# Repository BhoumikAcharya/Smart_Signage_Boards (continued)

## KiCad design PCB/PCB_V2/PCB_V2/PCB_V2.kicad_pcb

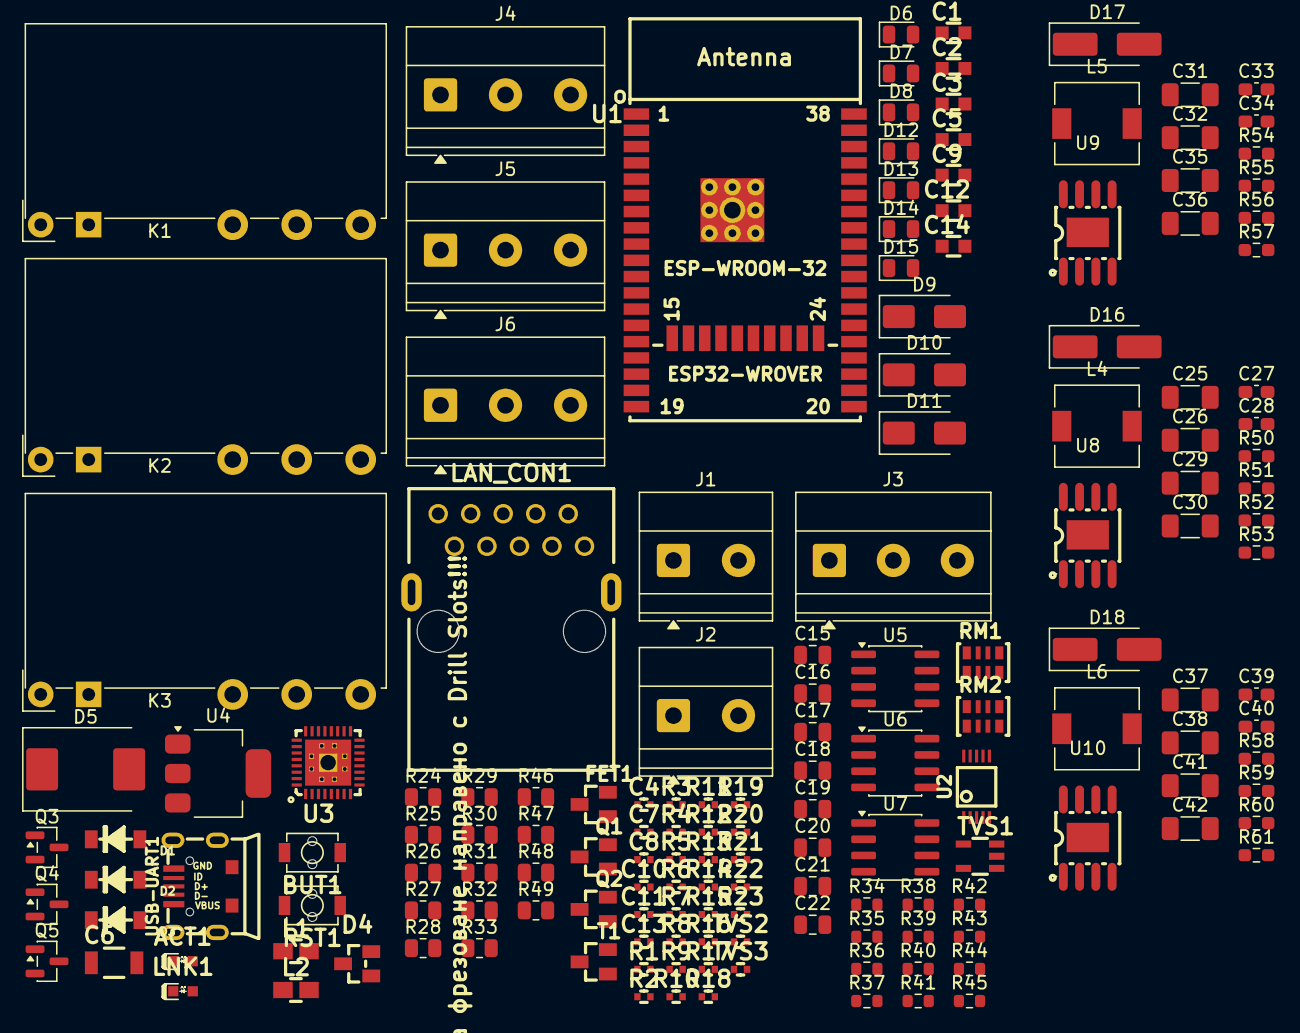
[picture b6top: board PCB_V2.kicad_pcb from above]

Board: 2 copper layers, 161 parts (0 on the bottom side), 116 nets, no tracks yet.

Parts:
ACT1: LED/YELLOW/0603; LED_0603_KA
BUT1: IT1185AU2; IT1185AU2_V2
C1, C3, C5, C9: 22uF/6.3V/20%/X5R/C0603; C_0603_5MIL_DWS
C2: 1uF/10V/20%/X5R/C0603; C_0603_5MIL_DWS
C4, C7, C8, C10, C11, C13: 100nF/10V/20%/X5R/C04020; C_0402_5MIL_DWS
C6: 1nF/2000V/10%/X7R/C1206; C_1206_5MIL_DWS_ISO
C12: 2.2uF/6.3V/10%/X5R/C0603; C_0603_5MIL_DWS
C14: NA(10uF/6.3V/20%/X5R/C0603); C_0603_5MIL_DWS
C15: 10uF; C_0805_2012Metric
C16, C17, C18: 100nF; C_0805_2012Metric
C19, C20, C21: 1nF; C_0805_2012Metric
C22: 22uF; C_0805_2012Metric
C25, C26, C31, C32, C37, C38: 10uF; C_1206_3216Metric_Pad1.33x1.80mm_HandSolder
C27, C33, C39: 100nF; C_0603_1608Metric_Pad1.08x0.95mm_HandSolder
C28, C34, C40: 220pF; C_0603_1608Metric_Pad1.08x0.95mm_HandSolder
C29, C30, C35, C36, C41, C42: 22uF; C_1206_3216Metric_Pad1.33x1.80mm_HandSolder
D1, D2, D3: 1N5819S4(SOD-123); SOD-123_1C-2A_KA
D4: BAT54C(SOT23-3); SOT23-3
D5: SS54; D_SMC
D6, D7, D8, D12, D13, D14, D15: LED; LED_0805_2012Metric
D9, D10, D11: M7; D_SMA
D16, D17, D18: D_SMA_Handsoldering
FET1: WPM2015-3/TR; SOT23
J1: PSU_I/P; TerminalBlock_Phoenix_MKDS-1,5-2-5.08_1x02_P5.08mm_Horizont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
J2: Battery_I/P; TerminalBlock_Phoenix_MKDS-1,5-2-5.08_1x02_P5.08mm_Horizont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
J3: LEDs Ground; TerminalBlock_Phoenix_MKDS-1,5-3_1x03_P5.00mm_Horizontal
J4: Relay_1_Terminal; TerminalBlock_Phoenix_MKDS-1,5-3-5.08_1x03_P5.08mm_Horizont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
J5: Relay_2_Terminal; TerminalBlock_Phoenix_MKDS-1,5-3-5.08_1x03_P5.08mm_Horizont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
J6: Relay_3_Terminal; TerminalBlock_Phoenix_MKDS-1,5-3-5.08_1x03_P5.08mm_Horizont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
K1, K2, K3: FINDER-34.51.7xxx.x019; Relay_SPDT_Finder_34.51_Horizontal
L1, L2: FB0805/600R/2A; L_0805_5MIL_DWS
L4, L5, L6: 6.8uH; L_6.3x6.3_H3
LAN_CON1: RJP-003TC1(LPJ4112CNL)
LNK1: LED/GREEN/0603; LED_0603_KA
Q1, Q2: BC817-40(SOT23); SOT23
Q3, Q4, Q5: BC846; SOT-23
R1, R2, R8, R9, R19, R22: 10k/R0402; R_0402_5MIL_DWS
R3, R13, R14: 1k/R0402; R_0402_5MIL_DWS
R4, R5, R6, R7: 49.9R/1%/R0402; R_0402_5MIL_DWS
R10, R11, R17: 2.2k/R0402; R_0402_5MIL_DWS
R12: 4.7k/R0402; R_0402_5MIL_DWS
R15, R23: NA/R0402; R_0402_5MIL_DWS
R16, R21: 220R/R0402; R_0402_5MIL_DWS
R18: NA(10k/R0402); R_0402_5MIL_DWS
R20: 12.1k/1%/R0402; R_0402_5MIL_DWS
R24, R25, R26, R31, R33: 2.2k; R_0805_2012Metric
R27, R28, R29: 3.3k; R_0805_2012Metric
R30, R32: 10k; R_0805_2012Metric
R34, R35, R36: 300; R_0603_1608Metric
R37, R38, R39: 1k; R_0603_1608Metric
R40, R42: 140k; R_0603_1608Metric
R41, R43, R45: 10k; R_0603_1608Metric
R44: 52.3k; R_0603_1608Metric
R46, R47, R48, R49: 1k; R_0805_2012Metric
R50, R54, R58: 100k; R_0603_1608Metric_Pad0.98x0.95mm_HandSolder
R51, R55, R59: 24.9k; R_0603_1608Metric_Pad0.98x0.95mm_HandSolder
R52, R56, R60: 200k; R_0603_1608Metric_Pad0.98x0.95mm_HandSolder
R53, R57, R61: 68.1k; R_0603_1608Metric_Pad0.98x0.95mm_HandSolder
RM1, RM2: RA1206_(4X0603)_4B8_2.2k; R_MATRIX_4
RST1: IT1185AU2; IT1185AU2_V2
T1: LMUN2211LT1G(SOT-23); SOT23
TVS1: ESDS314DBVR(SOT-23-5); SOT-23-5
TVS2, TVS3: NA(GG0402052R542P); D_0402_5MIL_DWS
U1: ESP32-WROOM-32E-N4; ESP32-WROVER_MODULE
U2: CH340X(MSOP-10); MSOP-10_Pitch-0.5mm_3.00x3.00x1.00mm
U3: LAN8710A-EZC(QFN32); QFN32_EP(33)_5.00x5.00x0.90mm_Pitch_0.50mm
U4: AMS1117-3.3; SOT-223-3_TabPin2
U5, U6, U7: ACS712xLCTR-20A; SOIC-8_3.9x4.9mm_P1.27mm
U8, U9, U10: MP1584EN; SOIC-8_L4.9-W3.9-P1.27-LS6.0-BL-EP3.3
USB-UART1: MISB-SWMM-5B-LF(USB_MICRO); USB-MICRO_MISB-SWMM-5B_LF

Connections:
+3.3V: C1.1, FET1.2, R1.1, R2.1, R15.2, R18.2, R22.1
+3.3VLAN: C5.1, C8.1, FET1.3, L2.1, R19.2, RM1.1.1, RM1.2.1, RM1.3.1, RM1.4.1, RM2.3.1, U3.12 (VDDIO)
+14.5V: D5.2 (A), J1.1, R30.1
/+5V_USB: C3.1, R8.1, U2.7 (VCC), USB-UART1.1 (VBUS)
/D+: U2.1 (UD+), USB-UART1.3 (D+)
/D-: U2.2 (UD-), USB-UART1.2 (D-)
/D_Com: D4.3 (CC), R16.2, R23.2
/ESP_EN: C2.1, D3.2 (A), R2.2, RST1.1, U1.3 (EN)
/GPI34\BUT1: BUT1.1, R22.2, R23.1, U1.6 (GPI34/ADC1_CH6/RTC_GPIO4)
/GPIO0: D4.2 (A2), R15.1, U1.25 (GPIO0/ADC2_CH1/TOUCH1/RTC_GPIO11/CLK_OU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)
/GPIO1\U0TXD: D2.1 (K), U1.35 (GPIO1/U0TXD/CLK_OUT3/EMAC_RXD2)
/GPIO2\HS2_DATA0: D4.1 (A1), U1.24 (GPIO2/ADC2_CH2/TOUCH2/RTC_GPIO12/HSPIWP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)
/GPIO3\U0RXD: D1.2 (A), R9.2, R18.1, U1.34 (GPIO3/U0RXD/CLK_OUT2)
/GPIO17\EMAC_CLK_OUT_180: U1.28 (NC(GPIO17/HS1_DATA5/U2TXD/EMAC_CLK_OUT_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), U3.5 (XTAL1/CLKIN)
/GPIO18\MDIO(RMII): RM1.4.2, U1.30 (GPIO18/VSPICLK/HS1_DATA7), U3.16 (MDIO)
/GPIO19\EMAC_TXD0(RMII): U1.31 (GPIO19/VSPIQ/U0CTS/EMAC_TXD0), U3.22 (TXD0)
/GPIO21\EMAC_TX_EN(RMII): U1.33 (GPIO21/VSPIHD/EMAC_TX_EN), U3.21 (TXEN)
/GPIO22\EMAC_TXD1(RMII): U1.36 (GPIO22/VSPIWP/U0RTS/EMAC_TXD1), U3.23 (TXD1)
/GPIO23\MDC(RMII): U1.37 (GPIO23/VSPID/HS1_STROBE), U3.17 (MDC)
/GPIO25\EMAC_RXD0(RMII): RM1.2.2, U1.10 (GPIO25/DAC_1/ADC2_CH8/RTC_GPIO6/EMAC_RX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), U3.11 (RXD0/MODE0)
/GPIO26\EMAC_RXD1(RMII): RM1.1.2, U1.11 (GPIO26/DAC_2/ADC2_CH9/RTC_GPIO7/EMAC_RX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), U3.10 (RXD1/MODE1)
/GPIO27\EMAC_RX_CRS_DV: RM2.3.2, U1.12 (GPIO27/ADC2_CH7/TOUCH7/RTC_GPIO17/EMAC_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), U3.15 (COL/CRS_DV/MODE2)
/MP1584ENCircuit1/Feedback: R40.2, R41.1, U9.4 (FB)
/MP1584ENCircuit2/Feedback: R42.2, R43.1, U10.4 (FB)
/MP1584ENCircuit/Feedback: R44.2, R45.1, U8.4 (FB)
/RD+: LAN_CON1.3 (RD+), R5.2, TVS1.1 (I/O1), TVS3.1 (IO1), U3.31 (RXP)
/RD-: LAN_CON1.6 (RD-), R4.2, TVS1.5 (I/O4), TVS3.2 (IO2), U3.30 (RXN)
/TD+: LAN_CON1.1 (TD+), R7.2, TVS1.3 (I/O2), TVS2.2 (IO2), U3.29 (TXP)
/TD-: LAN_CON1.2 (TD-), R6.2, TVS1.4 (I/O3), TVS2.1 (IO1), U3.28 (TXN)
AMS1117_O/P: C22.1, R46.2, U1.2 (VDD33(3V3)), U4.2 (VO)
BATT_VD: R32.2, R33.1, U1.5 (GPI39/SENSOR_VN/ADC1_CH3/RTC_GPIO3)
BC1_5_O/P: C15.1, C16.1, C17.1, C18.1, C29.1, C30.1, D9.1 (K), D10.1 (K), D11.1 (K), K1.A1, K2.A1, K3.A1, L4.2, R34.1, R35.1, R36.1, R44.1, R47.2, U4.3 (VI), U5.8 (VCC), U6.8 (VCC), U7.8 (VCC)
BC2_12_O/P_1: C35.1, C36.1, L5.2, R40.1, R48.2, U5.1 (IP+), U5.2 (IP+)
BC3_12_O/P_2: C41.1, C42.1, L6.2, R42.1, R49.2, U6.1 (IP+), U6.2 (IP+), U7.1 (IP+), U7.2 (IP+)
COM1: J4.2, K1.11, U5.3 (IP-), U5.4 (IP-)
COM2: J5.2, K2.11, U6.3 (IP-), U6.4 (IP-)
COM3: J6.2, K3.11, U7.3 (IP-), U7.4 (IP-)
CURRENT_SENSE_1: R24.2, R27.1, U1.9 (GPIO33/XTAL_32K_N/ADC1_CH5/TOUCH8/RTC_G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)
CURRENT_SENSE_2: R25.2, R28.1, U1.7 (GPI35/ADC1_CH7/RTC_GPIO5)
CURRENT_SENSE_3: R26.2, R29.1, U1.8 (GPIO32/XTAL_32K_P/ADC1_CH4/TOUCH9/RTC_G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)
GND: C2.2, C3.2, C4.2, C5.2, C6.1, C7.2, C8.2, C9.2, C10.2, C11.2, C12.2, C13.2, C14.1, C15.2, C16.2, C17.2, C18.2, C19.2, C20.2, C21.2, C22.2, C25.2, C26.2, C29.2, C30.2, C31.2, C32.2, C35.2, C36.2, C37.2, C38.2, C41.2, C42.2, D12.1 (K), D13.1 (K), D14.1 (K), D15.1 (K), D16.2 (A), D17.2 (A), D18.2 (A), J1.2, J2.2, J3.1, J3.2, J3.3, L1.2, LAN_CON1.7 (GND/NC), LAN_CON1.8 (NC/GND), Q3.3 (E), Q4.3 (E), Q5.3 (E), R11.2, R17.1, R20.2, R21.2, R27.2, R28.2, R29.2, R31.2, R33.2, R41.2, R43.2, R45.2, R51.2, R52.2, R53.2, R55.2, R56.2, R57.2, R59.2, R60.2, R61.2, RM2.1.1, RM2.2.1, RST1.2, T1.2 (E), TVS1.2 (GND), U1.1 (GND), U1.15 (GND), U1.38 (GND), U1.39 (THERMAL_PAD), U2.3 (GND), U3.24 (TXD2), U3.25 (TXD3), U3.33 (GND), U4.1 (GND), U5.5 (GND), U6.5 (GND), U7.5 (GND), U8.5 (GND), U8.9 (GND), U9.5 (GND), U9.9 (GND), U10.5 (GND), U10.9 (GND), USB-UART1.5 (GND)
MAIN_OP: C25.1, C26.1, C31.1, C32.1, C37.1, C38.1, D5.1 (K), J2.1, R32.1, R50.1, R54.1, R58.1, U8.7 (VIN), U9.7 (VIN), U10.7 (VIN)
NC1: J4.1, K1.12
NC2: J5.1, K2.12
NC3: J6.1, K3.12
NO1: J4.3, K1.14
NO2: J5.3, K2.14
NO3: J6.3, K3.14
unnamed: ACT1.2 (A), U3.3 (LED1/REGOFF)
unnamed: ACT1.1 (K), R11.1
unnamed: BUT1.2, R21.1
unnamed: C1.2, FET1.1, R1.2, R3.1
unnamed: C28.2, R53.1
unnamed: C34.2, R57.1
unnamed: C40.2, R61.1
unnamed: D1.1 (K), U2.8 (TXD)
unnamed: D2.2 (A), R8.2, U2.9 (RXD)
unnamed: D3.1 (K), Q1.3 (C)
unnamed: D6.2 (A), R34.2
unnamed: D6.1 (K), D9.2 (A), K1.A2, Q3.1 (C)
unnamed: D7.2 (A), R35.2
unnamed: D8.2 (A), R36.2
unnamed: D7.1 (K), D10.2 (A), K2.A2, Q4.1 (C)
unnamed: D8.1 (K), D11.2 (A), K3.A2, Q5.1 (C)
unnamed: D12.2 (A), R46.1
unnamed: D13.2 (A), R47.1
unnamed: D14.2 (A), R48.1
unnamed: D15.2 (A), R49.1
unnamed: C27.1, D16.1 (K), L4.1, U8.1 (SW)
unnamed: C33.1, D17.1 (K), L5.1, U9.1 (SW)
unnamed: C39.1, D18.1 (K), L6.1, U10.1 (SW)
unnamed: L1.1, USB-UART1.0
unnamed: C7.1, C9.1, C10.1, C11.1, L2.2, LAN_CON1.4 (TCT), LAN_CON1.5 (RCT), R4.1, R5.1, R6.1, R7.1, R10.1, U3.1 (VDD2A), U3.27 (VDD1A)
unnamed: C6.2, LAN_CON1.0 (Shield)
unnamed: LNK1.2 (A), R10.2
unnamed: LNK1.1 (K), U3.2 (LED2/NINTSEL)
unnamed: Q1.1 (B), R13.2
unnamed: Q1.2 (E), R14.1, U2.4 (RTS#)
unnamed: Q2.1 (B), R14.2
unnamed: Q2.3 (C), R16.1
unnamed: Q2.2 (E), R12.1, R13.1, U2.6 (TNOW/DTR#)
unnamed: Q3.2 (B), R37.1
unnamed: Q4.2 (B), R38.1
unnamed: Q5.2 (B), R39.1
unnamed: R3.2, T1.3 (C)
unnamed: R12.2, U2.5 (CTS#)
unnamed: C4.1, R9.1, U2.10 (V3)
unnamed: C14.2, R19.1, U3.19 (NRST)
unnamed: R20.1, U3.32 (RBIAS)
unnamed: RM2.1.2, U3.7 (RXCLK/PHYAD1)
unnamed: RM1.3.2, U3.9 (RXD2/RMIISEL)
unnamed: RM2.2.2, U3.8 (RXD3/PHYAD2)
unnamed: R17.2, U3.13 (RXER/RXD4/PHYAD0)
unnamed: C12.1, C13.1, U3.6 (VDDCR)
unnamed: C19.1, U5.6 (FILTER)
unnamed: R24.1, U5.7 (VIOUT)
unnamed: C20.1, U6.6 (FILTER)
unnamed: R25.1, U6.7 (VIOUT)
unnamed: C21.1, U7.6 (FILTER)
unnamed: R26.1, U7.7 (VIOUT)
unnamed: C27.2, U8.8 (BST)
unnamed: C28.1, U8.3 (COMP)
unnamed: R50.2, R51.1, U8.2 (EN)
unnamed: R52.1, U8.6 (FREQ)
unnamed: C33.2, U9.8 (BST)
unnamed: C34.1, U9.3 (COMP)
unnamed: R54.2, R55.1, U9.2 (EN)
unnamed: R56.1, U9.6 (FREQ)
unnamed: C39.2, U10.8 (BST)
unnamed: C40.1, U10.3 (COMP)
unnamed: R58.2, R59.1, U10.2 (EN)
unnamed: R60.1, U10.6 (FREQ)
PSU_ESP: R30.2, R31.1, U1.4 (GPI36/SENSOR_VP/ADC1_CH0/RTC_GPIO0)
RELAY_1_CTRL: R37.2, U1.26 (GPIO4/ADC2_CH0/TOUCH0/RTC_GPIO10/HSPIHD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)
RELAY_2_CTRL: R38.2, U1.16 (GPIO13/ADC2_CH4/TOUCH4/RTC_GPIO14/MTCK/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)
RELAY_3_CTRL: R39.2, U1.14 (GPIO12/ADC2_CH5/TOUCH5/RTC_GPIO15/MTDI/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)

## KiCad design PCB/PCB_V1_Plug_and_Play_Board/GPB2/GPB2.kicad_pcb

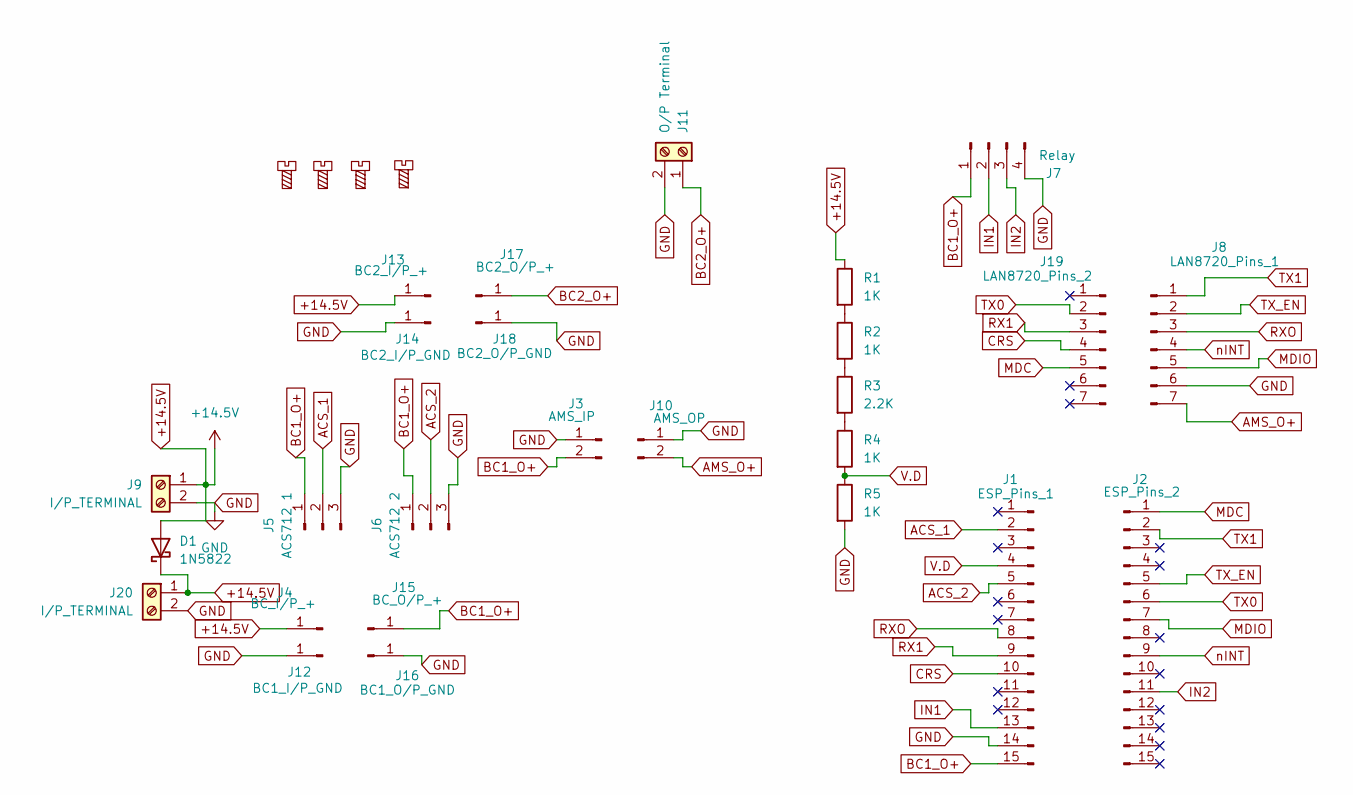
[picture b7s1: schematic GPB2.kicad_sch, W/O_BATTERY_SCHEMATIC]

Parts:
D1: 1N5822; D_DO-201AD_P15.24mm_Horizontal
H1, H2, H3, H4: MountingScrew; MountingHole_3.2mm_M3
J1: ESP_Pins_1; PinSocket_1x15_P2.54mm_Vertical
J2: ESP_Pins_2; PinSocket_1x15_P2.54mm_Vertical
J3: AMS_IP; PinSocket_1x02_P2.54mm_Vertical
J4: BC_I/P_+; PinSocket_1x01_P2.54mm_Vertical
J5: ACS712 1; PinSocket_1x03_P2.54mm_Vertical
J6: ACS712 2; PinSocket_1x03_P2.54mm_Vertical
J7: Relay; PinHeader_1x04_P2.54mm_Vertical
J8: LAN8720_Pins_1; PinSocket_1x07_P2.54mm_Vertical
J9, J20: I/P_TERMINAL; TerminalBlock_Phoenix_MKDS-1,5-2-5.08_1x02_P5.08mm_Horizont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
J10: AMS_OP; PinSocket_1x02_P2.54mm_Vertical
J11: O/P Terminal; TerminalBlock_Phoenix_MKDS-1,5-2-5.08_1x02_P5.08mm_Horizont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
J12: BC1_I/P_GND; PinSocket_1x01_P2.54mm_Vertical
J13: BC2_I/P_+; PinSocket_1x01_P2.54mm_Vertical
J14: BC2_I/P_GND; PinSocket_1x01_P2.54mm_Vertical
J15: BC_O/P_+; PinSocket_1x01_P2.54mm_Vertical
J16: BC1_O/P_GND; PinSocket_1x01_P2.54mm_Vertical
J17: BC2_O/P_+; PinSocket_1x01_P2.54mm_Vertical
J18: BC2_O/P_GND; PinSocket_1x01_P2.54mm_Vertical
J19: LAN8720_Pins_2; PinSocket_1x07_P2.54mm_Vertical
R1, R2, R4, R5: 1K; R_Axial_DIN0207_L6.3mm_D2.5mm_P10.16mm_Horizontal
R3: 2.2K; R_Axial_DIN0309_L9.0mm_D3.2mm_P12.70mm_Horizontal

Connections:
+14.5V: D1.1 (K), D1.2 (A), J4.1, J9.1 (V+), J13.1, J20.1 (V+), R1.1
ACS_1: J1.2 (Vp), J5.2 (OUT)
ACS_2: J1.5 (D35), J6.2 (OUT)
AMS_O+: J8.7, J10.2 (GND)
BC1_O+: J1.15 (VIN), J3.2 (GND), J5.1 (VCC), J6.1 (VCC), J7.1 (VCC), J15.1
BC2_O+: J11.1 (V+), J17.1
CRS: J1.10 (D27), J19.4
GND: J1.14 (GND), J3.1 (I+), J5.3 (GND), J6.3 (GND), J7.4 (GND), J8.6, J9.2 (V-), J10.1 (O+), J11.2 (V-), J12.1, J14.1, J16.1, J18.1, J20.2 (V-), R5.2
IN1: J1.13 (D13), J7.2 (IN2)
IN2: J2.11 (D4), J7.3 (IN1)
MDC: J2.1 (D23), J19.5
MDIO: J2.7 (D18), J8.5
unnamed: R1.2, R2.1
unnamed: R2.2, R3.1
unnamed: R3.2, R4.1
RX1: J1.9 (D26), J19.3
RXO: J1.8 (D25), J8.3
TX0: J2.6 (D19), J19.2
TX1: J2.2 (D22), J8.1
TX_EN: J2.5 (D21), J8.2
V.D: J1.4 (D34), R4.2, R5.1
nINT: J2.9 (TX2), J8.4

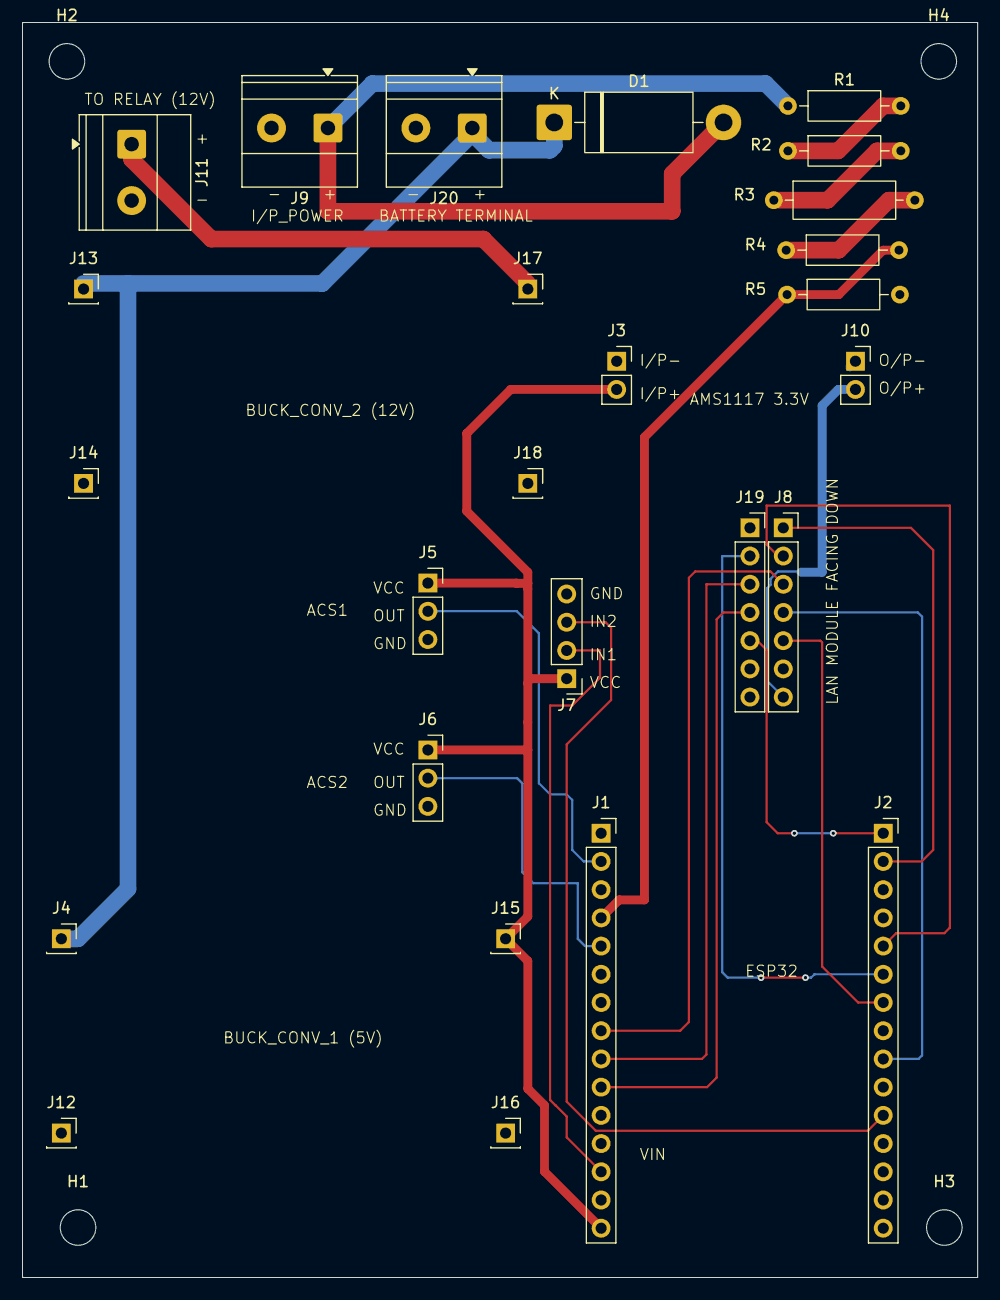
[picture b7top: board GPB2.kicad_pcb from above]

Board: 2 copper layers, 86.0 x 113.0 mm, 30 parts (0 on the bottom side), 22 nets.

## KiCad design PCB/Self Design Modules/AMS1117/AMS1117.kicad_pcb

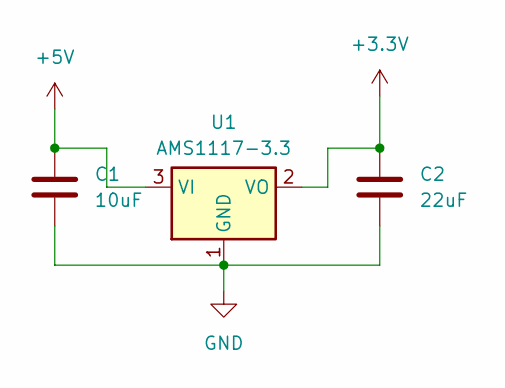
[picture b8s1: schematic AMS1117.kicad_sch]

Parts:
C1: 10uF; C_0805_2012Metric
C2: 22uF; C_0805_2012Metric
U1: AMS1117-3.3; SOT-223-3_TabPin2

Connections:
+3.3V: C2.1, U1.2 (VO)
+5V: C1.1, U1.3 (VI)
GND: C1.2, C2.2, U1.1 (GND)

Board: 2 copper layers, 3 parts (0 on the bottom side), 3 nets, no tracks yet.

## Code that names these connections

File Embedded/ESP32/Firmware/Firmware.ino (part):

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 *     reflash step disappears. Nothing else has to change.
 *
 * WHAT CHANGED FROM v2.0 (all deliberate, see esp32_contract.md §8):
 *   1.  I2C moved 16/17 -> 4/13. GPIO17 is the LAN8720 50MHz clock.
 *   2.  4th ACS712 added (GPIO33, Static Zone 2) + 'current4' topic.
 *   3.  Modes 4/5/6 added. MODE 4 CHANGED MEANING: was solid-ON-all, now
 *       solid-ON-LEFT. Old solid-ON-all is now mode 6. Clear retained 'value'
 *       topics on the broker before flashing or a stale retained 4 lights the
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    Serial.println(mcpHealthy ? F("OK") : F("FOUND BUT READBACK FAILED"));
  } else {
    Serial.println(F("NOT FOUND — continuing anyway, will retry in background."));
    Serial.println(F("Check: SDA=GPIO4, SCL=GPIO13, 4.7k pull-ups, RESET->3V3, A0/A1/A2->GND."));
  }

  sensorQueue = xQueueCreate(1, sizeof(NodeStateMsg));
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
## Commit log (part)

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2026-04-29 Deleted the readme
2026-05-05 new documentation added.
2026-05-05 Removed old documentation
2026-05-06 Adding the HMI documentation to teh HMI folder
2026-05-06 had pasted an empty file, changed that to the required file
2026-05-06 Created a repo for version history of the HMI and added V1.zip
2026-05-06 Added version history for the ESP32 and the Raspberrypi codes along with the documentation in .md files
2026-05-06 Made a builds folder, for the currently working setup 1.Battery 2. V1 of the HMI 3. Pi without the ON/OFF fucntionality
2026-05-06 Uploaded the latest windows form application v1.3; Upload the latest documentation; Also uploaded the Customized Arduino code of the firmware - under development.
2026-06-03 Initial COmmit of the PCB Design files
2026-06-07 Changes Part 1 for the PCB Files
    Most recent update for the PCB Design
2026-06-07 Updatign the files of the PCB folder
    - seld design modules completed, with the correct math
    - schematic for pcb v2 completed
2026-06-07 Part3_PCB_Files
2026-06-08 Updated the documentation in the software Node Calibration
2026-06-10 Pushing most recent changes - 10/6/2026
    1. Finished the schematics of all the individual modules
    2. Made the changes to errors and the hierarchal issues for the MP1584
    3. Fixed the open connections for the OLIMEX ESP32 and the labeling for the same
    TO DO//
    1. Check the current warnings while running ERC (single label warnings and the no connect ones)
    2. The tracing and component placement needs to be finalised
2026-06-11 Uploading the old plug and play PCB files into the PCB folder
    1. Added the old PCB files into the PCB folder
    2. Made minute changes to the original PCB
2026-06-18 Created version history
    1. Version history for the ESP32
    2. Version history for the current pi code
    3. Added the animation code into testing and calibration
    Will add the new ESp32 and the Raspberrypi code next, so created a backup of current progress
2026-06-22 Pushing the boilerplate code for the new ESP32 and RaspberryPI codes
    1. This is the first set of the codes of the ESP32 and the RaspberryPi
    2. The proper merged code and documentation will be provided in the next commit. That will include boilerplate code + the communication fucntionality
    3. The rest of the thought process and the documentation is provided in the WA group, will add the Ipad notes, as running notes later on as well
2026-06-22 Updating the updated code for the ESP32 and the Raspberrypi
    Updated code with final functionality of the LED animation, communication updated here:
    1. The documentation is in the .md file of each pi and esp32
2026-06-26 Uploading the recent batch of files
    1. Schematic of the new PCB (ESP32 and LAN connections need to be made )
    2. Data sheets for the components
    3. Connection .md file
2026-06-26 removing the lcoal storage files
2026-06-27 Committing the Final schematic file along with the
    1. ESP32 connections made along with the LAN8720 module
    2. Footprints assigned for all the individual components
    3. Need to recheck and analyse the connections a 3rd and 4th time
    5. Need to figure out component placement, on the PCB and close the tracing
2026-06-29 Removing the untitled file i uploaded by mistake
2026-06-29 Uploading the JTAG files and updated the footprints for the resistors
